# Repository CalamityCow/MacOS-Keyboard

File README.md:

# MacOS-Keyboard

Fully custom MacOS keyboard with 101 keys, 6 macro keys, 101 leds, and a volume knob. Planning to add a screen and hubs later. 

BOM: https://docs.google.com/spreadsheets/d/1dYup_cxLSYAhRu9MLTjsDp3llwcmy9G50tkykbGbxao/edit?gid=810680966#gid=810680966

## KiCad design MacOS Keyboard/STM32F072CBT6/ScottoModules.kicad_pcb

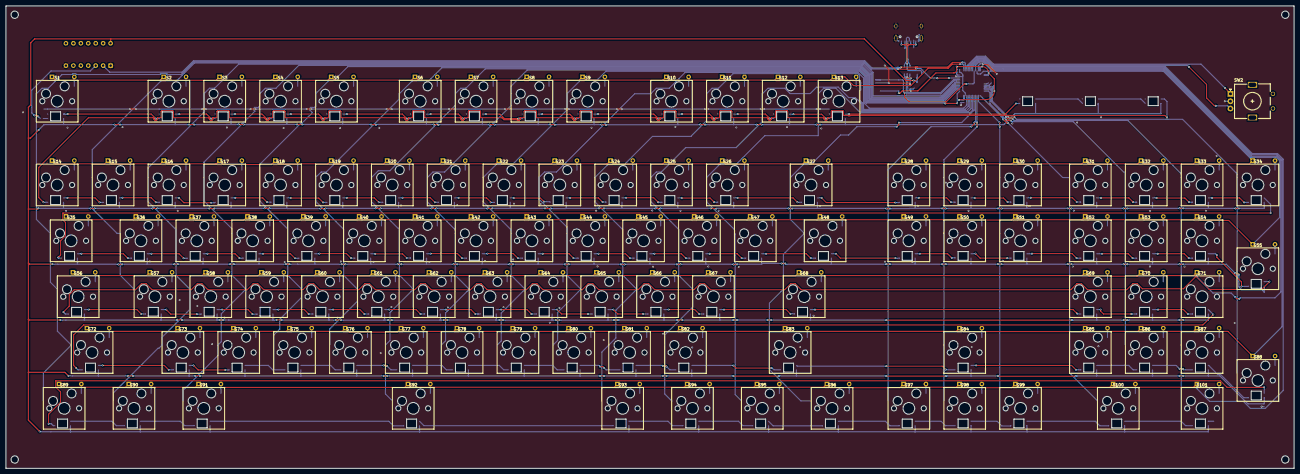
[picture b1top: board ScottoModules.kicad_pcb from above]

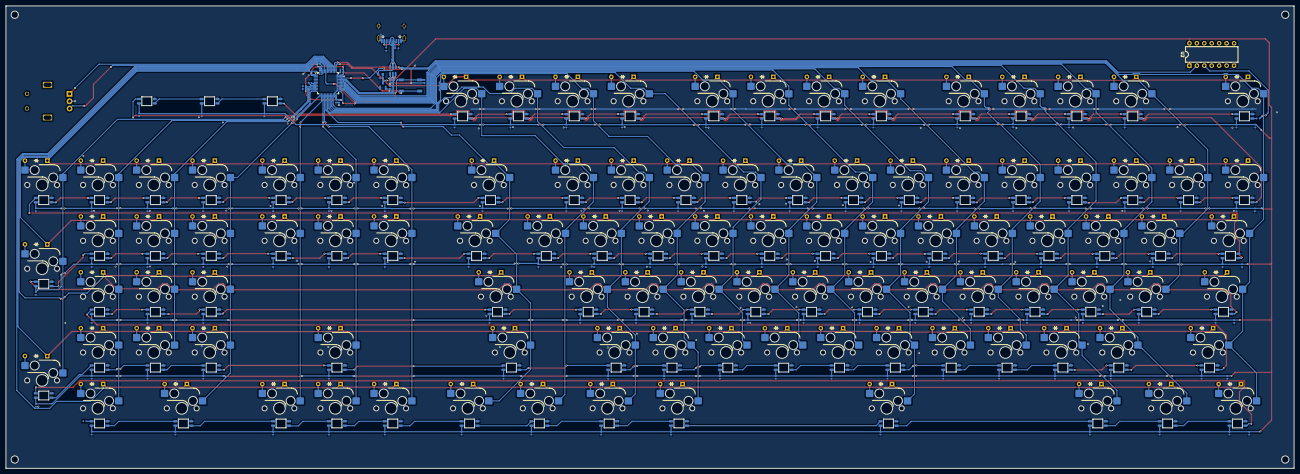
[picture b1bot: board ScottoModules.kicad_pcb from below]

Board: 2 copper layers, 439.4 x 157.7 mm, 440 parts (338 on the bottom side), 249 nets.

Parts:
C7, C10, C11, C13, C16: 100nF; Capacitor_0402
C8, C9, C15: 1uF; Capacitor_0402
C12, C17: 4.7uF; Capacitor_0402
C14: 10nF; Capacitor_0402
D1, D2, D3, D4, D5, D6, D7, D8, D9, D10, D11, D12, D13, D14, D15, D16, D17, D18, D19, D20, D21, D22, D23, D24, D25, D26, D27, D28, D29, D30, D31, D32, D33, D34, D35, D36, D37, D38, D39, D40, D41, D42, D43, D44, D45, D46, D47, D48, D49, D50, D51, D52, D53, D54, D55, D56, D57, D58, D59, D60, D61, D62, D63, D64, D65, D66, D67, D68, D69, D70, D71, D72, D73, D74, D75, D76, D77, D78, D79, D80, D81, D82, D83, D84, D85, D86, D87, D88, D89, D90, D91, D92, D93, D94, D95, D96, D97, D98, D99, D100, D101: Diode; Diode_DO-35
DisplayLED1, DisplayLED2, DisplayLED3: SK6812MINI; LED_SK6812MINI
DisplayLEDCAP1, DisplayLEDCAP2, DisplayLEDCAP3: 100nF; Capacitor_0402
F1: 500mA; Fuse_0603
J1: USB_C; USB_C_HRO_TYPE-C-31-M-12
LED1, LED2, LED3, LED4, LED5, LED6, LED7, LED8, LED9, LED10, LED11, LED12, LED13, LED14, LED15, LED16, LED17, LED18, LED19, LED20, LED21, LED22, LED23, LED24, LED25, LED26, LED27, LED28, LED29, LED30, LED31, LED32, LED33, LED34, LED35, LED36, LED37, LED38, LED39, LED40, LED41, LED42, LED43, LED44, LED45, LED46, LED47, LED48, LED49, LED50, LED51, LED52, LED53, LED54, LED55, LED56, LED57, LED58, LED59, LED60, LED61, LED62, LED63, LED64, LED65, LED66, LED67, LED68, LED69, LED70, LED71, LED72, LED73, LED74, LED75, LED76, LED77, LED78, LED79, LED80, LED81, LED82, LED83, LED84, LED85, LED86, LED87, LED88, LED89, LED90, LED91, LED92, LED93, LED94, LED95, LED96, LED97, LED98, LED99, LED100, LED101: SK6812MINI; LED_SK6812MINI
LEDBULKCAP1, LEDBULKCAP2, LEDBULKCAP3, LEDBULKCAP4, LEDBULKCAP5, LEDBULKCAP6: 100uF; Capacitor_0402
LEDCAP1, LEDCAP2, LEDCAP3, LEDCAP4, LEDCAP5, LEDCAP6, LEDCAP7, LEDCAP8, LEDCAP9, LEDCAP10, LEDCAP11, LEDCAP12, LEDCAP13, LEDCAP14, LEDCAP15, LEDCAP16, LEDCAP17, LEDCAP18, LEDCAP19, LEDCAP20, LEDCAP21, LEDCAP22, LEDCAP23, LEDCAP24, LEDCAP25, LEDCAP26, LEDCAP27, LEDCAP28, LEDCAP29, LEDCAP30, LEDCAP31, LEDCAP32, LEDCAP33, LEDCAP34, LEDCAP35, LEDCAP36, LEDCAP37, LEDCAP38, LEDCAP39, LEDCAP40, LEDCAP41, LEDCAP42, LEDCAP43, LEDCAP44, LEDCAP45, LEDCAP46, LEDCAP47, LEDCAP48, LEDCAP49, LEDCAP50, LEDCAP51, LEDCAP52, LEDCAP53, LEDCAP54, LEDCAP55, LEDCAP56, LEDCAP57, LEDCAP58, LEDCAP59, LEDCAP60, LEDCAP61, LEDCAP62, LEDCAP63, LEDCAP64, LEDCAP65, LEDCAP66, LEDCAP67, LEDCAP68, LEDCAP69, LEDCAP70, LEDCAP71, LEDCAP72, LEDCAP73, LEDCAP74, LEDCAP75, LEDCAP76, LEDCAP77, LEDCAP78, LEDCAP79, LEDCAP80, LEDCAP81, LEDCAP82, LEDCAP83, LEDCAP84, LEDCAP85, LEDCAP86, LEDCAP87, LEDCAP88, LEDCAP89, LEDCAP90, LEDCAP91, LEDCAP92, LEDCAP93, LEDCAP94, LEDCAP95, LEDCAP96, LEDCAP97, LEDCAP98, LEDCAP99, LEDCAP100, LEDCAP101: 100nF; Capacitor_0402
R1: 10k; Resistor_0402
R2, R3: 5.1k; Resistor_0402
R4, R5: 500R; Resistor_0402
S1, S2, S3, S4, S5, S6, S7, S8, S9, S10, S11, S12, S13, S14, S15, S16, S17, S18, S19, S20, S21, S22, S23, S24, S25, S26, S27, S28, S29, S30, S31, S32, S33, S34, S35, S36, S37, S38, S39, S40, S41, S42, S43, S44, S45, S46, S47, S48, S49, S50, S51, S52, S53, S54, S55, S56, S57, S58, S59, S60, S61, S62, S63, S64, S65, S66, S67, S68, S69, S70, S71, S72, S73, S74, S75, S76, S77, S78, S79, S80, S81, S82, S83, S84, S85, S86, S87, S88, S89, S90, S91, S92, S93, S94, S95, S96, S97, S98, S99, S100, S101: Keyswitch; Hotswap_MX_1.00u
SW1: SW_Push; Button_TL3342
SW2: RotaryEncoder; RotaryEncoder_Alps_EC11E_Vertical_H20mm
U1: STM32F072CBTx; LQFP-48_7x7mm_P0.5mm
U2: 74AHCT125; DIP-14_W7.62mm
U3: XC6206; Voltage_SOT-23
U4: USBLC6-2SC6; ESD_SOT-23-6

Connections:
+3.3V: C9.1, C10.2, C11.2, C12.2, C13.2, C14.2, C15.2, C16.2, C17.2, SW1.1, U1.1 (VBAT), U1.9 (VDDA), U1.24 (VDD), U1.36 (VDDIO2), U1.48 (VDD), U3.2 (VO)
+5V: C8.1, DisplayLED1.1 (VDD), DisplayLED2.1 (VDD), DisplayLED3.1 (VDD), DisplayLEDCAP1.1, DisplayLEDCAP2.1, DisplayLEDCAP3.1, F1.2, LED1.1 (VDD), LED2.1 (VDD), LED3.1 (VDD), LED4.1 (VDD), LED5.1 (VDD), LED6.1 (VDD), LED7.1 (VDD), LED8.1 (VDD), LED9.1 (VDD), LED10.1 (VDD), LED11.1 (VDD), LED12.1 (VDD), LED13.1 (VDD), LED14.1 (VDD), LED15.1 (VDD), LED16.1 (VDD), LED17.1 (VDD), LED18.1 (VDD), LED19.1 (VDD), LED20.1 (VDD), LED21.1 (VDD), LED22.1 (VDD), LED23.1 (VDD), LED24.1 (VDD), LED25.1 (VDD), LED26.1 (VDD), LED27.1 (VDD), LED28.1 (VDD), LED29.1 (VDD), LED30.1 (VDD), LED31.1 (VDD), LED32.1 (VDD), LED33.1 (VDD), LED34.1 (VDD), LED35.1 (VDD), LED36.1 (VDD), LED37.1 (VDD), LED38.1 (VDD), LED39.1 (VDD), LED40.1 (VDD), LED41.1 (VDD), LED42.1 (VDD), LED43.1 (VDD), LED44.1 (VDD), LED45.1 (VDD), LED46.1 (VDD), LED47.1 (VDD), LED48.1 (VDD), LED49.1 (VDD), LED50.1 (VDD), LED51.1 (VDD), LED52.1 (VDD), LED53.1 (VDD), LED54.1 (VDD), LED55.1 (VDD), LED56.1 (VDD), LED57.1 (VDD), LED58.1 (VDD), LED59.1 (VDD), LED60.1 (VDD), LED61.1 (VDD), LED62.1 (VDD), LED63.1 (VDD), LED64.1 (VDD), LED65.1 (VDD), LED66.1 (VDD), LED67.1 (VDD), LED68.1 (VDD), LED69.1 (VDD), LED70.1 (VDD), LED71.1 (VDD), LED72.1 (VDD), LED73.1 (VDD), LED74.1 (VDD), LED75.1 (VDD), LED76.1 (VDD), LED77.1 (VDD), LED78.1 (VDD), LED79.1 (VDD), LED80.1 (VDD), LED81.1 (VDD), LED82.1 (VDD), LED83.1 (VDD), LED84.1 (VDD), LED85.1 (VDD), LED86.1 (VDD), LED87.1 (VDD), LED88.1 (VDD), LED89.1 (VDD), LED90.1 (VDD), LED91.1 (VDD), LED92.1 (VDD), LED93.1 (VDD), LED94.1 (VDD), LED95.1 (VDD), LED96.1 (VDD), LED97.1 (VDD), LED98.1 (VDD), LED99.1 (VDD), LED100.1 (VDD), LED101.1 (VDD), LEDBULKCAP1.1, LEDBULKCAP2.1, LEDBULKCAP3.1, LEDBULKCAP4.1, LEDBULKCAP5.1, LEDBULKCAP6.1, LEDCAP1.1, LEDCAP2.1, LEDCAP3.1, LEDCAP4.1, LEDCAP5.1, LEDCAP6.1, LEDCAP7.1, LEDCAP8.1, LEDCAP9.1, LEDCAP10.1, LEDCAP11.1, LEDCAP12.1, LEDCAP13.1, LEDCAP14.1, LEDCAP15.1, LEDCAP16.1, LEDCAP17.1, LEDCAP18.1, LEDCAP19.1, LEDCAP20.1, LEDCAP21.1, LEDCAP22.1, LEDCAP23.1, LEDCAP24.1, LEDCAP25.1, LEDCAP26.1, LEDCAP27.1, LEDCAP28.1, LEDCAP29.1, LEDCAP30.1, LEDCAP31.1, LEDCAP32.1, LEDCAP33.1, LEDCAP34.1, LEDCAP35.1, LEDCAP36.1, LEDCAP37.1, LEDCAP38.1, LEDCAP39.1, LEDCAP40.1, LEDCAP41.1, LEDCAP42.1, LEDCAP43.1, LEDCAP44.1, LEDCAP45.1, LEDCAP46.1, LEDCAP47.1, LEDCAP48.1, LEDCAP49.1, LEDCAP50.1, LEDCAP51.1, LEDCAP52.1, LEDCAP53.1, LEDCAP54.1, LEDCAP55.1, LEDCAP56.1, LEDCAP57.1, LEDCAP58.1, LEDCAP59.1, LEDCAP60.1, LEDCAP61.1, LEDCAP62.1, LEDCAP63.1, LEDCAP64.1, LEDCAP65.1, LEDCAP66.1, LEDCAP67.1, LEDCAP68.1, LEDCAP69.1, LEDCAP70.1, LEDCAP71.1, LEDCAP72.1, LEDCAP73.1, LEDCAP74.1, LEDCAP75.1, LEDCAP76.1, LEDCAP77.1, LEDCAP78.1, LEDCAP79.1, LEDCAP80.1, LEDCAP81.1, LEDCAP82.1, LEDCAP83.1, LEDCAP84.1, LEDCAP85.1, LEDCAP86.1, LEDCAP87.1, LEDCAP88.1, LEDCAP89.1, LEDCAP90.1, LEDCAP91.1, LEDCAP92.1, LEDCAP93.1, LEDCAP94.1, LEDCAP95.1, LEDCAP96.1, LEDCAP97.1, LEDCAP98.1, LEDCAP99.1, LEDCAP100.1, LEDCAP101.1, U2.14 (VCC), U3.3 (VI)
/A15: U1.38 (PA15), U2.2
/B3: SW2.A, U1.39 (PB3)
/B4: SW2.B, U1.40 (PB4)
/BOOT0: R1.2, SW1.2, U1.44 (BOOT0)
/LED/DIN: R4.1, U2.3
/MCU_D+: U1.33 (PA12), U4.1 (I/O1)
/MCU_D-: U1.32 (PA11), U4.3 (I/O2)
/NRST: C7.1, U1.7 (NRST)
/USB_D+: J1.A6 (D+), J1.B6 (D+), U4.6 (I/O1)
/USB_D-: J1.A7 (D-), J1.B7 (D-), U4.4 (I/O2)
A0: S34.1, S55.1, S88.1, U1.10 (PA0)
A1: S33.1, S54.1, S71.1, S87.1, S101.1, U1.11 (PA1)
A2: S32.1, S53.1, S70.1, S86.1, U1.12 (PA2)
A3: S31.1, S52.1, S69.1, S85.1, S100.1, U1.13 (PA3)
A4: S30.1, S51.1, S99.1, U1.14 (PA4)
A5: S29.1, S50.1, S84.1, S98.1, U1.15 (PA5)
A6: S28.1, S49.1, S97.1, U1.16 (PA6)
A7: S27.1, S48.1, S68.1, S83.1, S96.1, U1.17 (PA7)
A8: S4.1, S17.1, S38.1, S59.1, S74.1, S91.1, U1.29 (PA8)
A9: S3.1, S16.1, S37.1, S58.1, S73.1, S90.1, U1.30 (PA9)
A10: S2.1, S15.1, S36.1, S57.1, U1.31 (PA10)
A13: S1.1, S14.1, S35.1, S56.1, S72.1, S89.1, U1.34 (PA13)
A14: D1.1 (K), D2.1 (K), D3.1 (K), D4.1 (K), D5.1 (K), D6.1 (K), D7.1 (K), D8.1 (K), D9.1 (K), D10.1 (K), D11.1 (K), D12.1 (K), D13.1 (K), U1.37 (PA14)
B0: S13.1, S26.1, S47.1, S95.1, U1.18 (PB0)
B1: S12.1, S25.1, S46.1, S67.1, S82.1, S94.1, U1.19 (PB1)
B2: S11.1, S24.1, S45.1, S66.1, S81.1, S93.1, U1.20 (PB2)
B5: D89.1 (K), D90.1 (K), D91.1 (K), D92.1 (K), D93.1 (K), D94.1 (K), D95.1 (K), D96.1 (K), D97.1 (K), D98.1 (K), D99.1 (K), D100.1 (K), D101.1 (K), U1.41 (PB5)
B6: D72.1 (K), D73.1 (K), D74.1 (K), D75.1 (K), D76.1 (K), D77.1 (K), D78.1 (K), D79.1 (K), D80.1 (K), D81.1 (K), D82.1 (K), D83.1 (K), D84.1 (K), D85.1 (K), D86.1 (K), D87.1 (K), D88.1 (K), U1.42 (PB6)
B7: D56.1 (K), D57.1 (K), D58.1 (K), D59.1 (K), D60.1 (K), D61.1 (K), D62.1 (K), D63.1 (K), D64.1 (K), D65.1 (K), D66.1 (K), D67.1 (K), D68.1 (K), D69.1 (K), D70.1 (K), D71.1 (K), U1.43 (PB7)
B8: D35.1 (K), D36.1 (K), D37.1 (K), D38.1 (K), D39.1 (K), D40.1 (K), D41.1 (K), D42.1 (K), D43.1 (K), D44.1 (K), D45.1 (K), D46.1 (K), D47.1 (K), D48.1 (K), D49.1 (K), D50.1 (K), D51.1 (K), D52.1 (K), D53.1 (K), D54.1 (K), D55.1 (K), U1.45 (PB8)
B9: D14.1 (K), D15.1 (K), D16.1 (K), D17.1 (K), D18.1 (K), D19.1 (K), D20.1 (K), D21.1 (K), D22.1 (K), D23.1 (K), D24.1 (K), D25.1 (K), D26.1 (K), D27.1 (K), D28.1 (K), D29.1 (K), D30.1 (K), D31.1 (K), D32.1 (K), D33.1 (K), D34.1 (K), U1.46 (PB9)
B10: S10.1, S23.1, S44.1, S65.1, S80.1, U1.21 (PB10)
B11: S9.1, S22.1, S43.1, S64.1, S79.1, U1.22 (PB11)
B12: S8.1, S21.1, S42.1, S63.1, S78.1, U1.25 (PB12)
B13: S7.1, S20.1, S41.1, S62.1, S77.1, S92.1, U1.26 (PB13)
B14: S6.1, S19.1, S40.1, S61.1, S76.1, U1.27 (PB14)
B15: S5.1, S18.1, S39.1, S60.1, S75.1, U1.28 (PB15)
D1: DisplayLED3.2 (DOUT), LED14.4 (DIN)
D2: LED34.2 (DOUT), LED35.4 (DIN)
D3: LED55.2 (DOUT), LED56.4 (DIN)
D4: LED71.2 (DOUT), LED72.4 (DIN)
D5: LED88.2 (DOUT), LED89.4 (DIN)
GND: C7.2, C8.2, C9.2, C10.1, C11.1, C12.1, C13.1, C14.1, C15.1, C16.1, C17.1, DisplayLED1.3 (VSS), DisplayLED2.3 (VSS), DisplayLED3.3 (VSS), DisplayLEDCAP1.2, DisplayLEDCAP2.2, DisplayLEDCAP3.2, J1.A1 (GND), J1.A12 (GND), J1.B1 (GND), J1.B12 (GND), J1.S1 (SHIELD), LED1.3 (VSS), LED2.3 (VSS), LED3.3 (VSS), LED4.3 (VSS), LED5.3 (VSS), LED6.3 (VSS), LED7.3 (VSS), LED8.3 (VSS), LED9.3 (VSS), LED10.3 (VSS), LED11.3 (VSS), LED12.3 (VSS), LED13.3 (VSS), LED14.3 (VSS), LED15.3 (VSS), LED16.3 (VSS), LED17.3 (VSS), LED18.3 (VSS), LED19.3 (VSS), LED20.3 (VSS), LED21.3 (VSS), LED22.3 (VSS), LED23.3 (VSS), LED24.3 (VSS), LED25.3 (VSS), LED26.3 (VSS), LED27.3 (VSS), LED28.3 (VSS), LED29.3 (VSS), LED30.3 (VSS), LED31.3 (VSS), LED32.3 (VSS), LED33.3 (VSS), LED34.3 (VSS), LED35.3 (VSS), LED36.3 (VSS), LED37.3 (VSS), LED38.3 (VSS), LED39.3 (VSS), LED40.3 (VSS), LED41.3 (VSS), LED42.3 (VSS), LED43.3 (VSS), LED44.3 (VSS), LED45.3 (VSS), LED46.3 (VSS), LED47.3 (VSS), LED48.3 (VSS), LED49.3 (VSS), LED50.3 (VSS), LED51.3 (VSS), LED52.3 (VSS), LED53.3 (VSS), LED54.3 (VSS), LED55.3 (VSS), LED56.3 (VSS), LED57.3 (VSS), LED58.3 (VSS), LED59.3 (VSS), LED60.3 (VSS), LED61.3 (VSS), LED62.3 (VSS), LED63.3 (VSS), LED64.3 (VSS), LED65.3 (VSS), LED66.3 (VSS), LED67.3 (VSS), LED68.3 (VSS), LED69.3 (VSS), LED70.3 (VSS), LED71.3 (VSS), LED72.3 (VSS), LED73.3 (VSS), LED74.3 (VSS), LED75.3 (VSS), LED76.3 (VSS), LED77.3 (VSS), LED78.3 (VSS), LED79.3 (VSS), LED80.3 (VSS), LED81.3 (VSS), LED82.3 (VSS), LED83.3 (VSS), LED84.3 (VSS), LED85.3 (VSS), LED86.3 (VSS), LED87.3 (VSS), LED88.3 (VSS), LED89.3 (VSS), LED90.3 (VSS), LED91.3 (VSS), LED92.3 (VSS), LED93.3 (VSS), LED94.3 (VSS), LED95.3 (VSS), LED96.3 (VSS), LED97.3 (VSS), LED98.3 (VSS), LED99.3 (VSS), LED100.3 (VSS), LED101.3 (VSS), LEDBULKCAP1.2, LEDBULKCAP2.2, LEDBULKCAP3.2, LEDBULKCAP4.2, LEDBULKCAP5.2, LEDBULKCAP6.2, LEDCAP1.2, LEDCAP2.2, LEDCAP3.2, LEDCAP4.2, LEDCAP5.2, LEDCAP6.2, LEDCAP7.2, LEDCAP8.2, LEDCAP9.2, LEDCAP10.2, LEDCAP11.2, LEDCAP12.2, LEDCAP13.2, LEDCAP14.2, LEDCAP15.2, LEDCAP16.2, LEDCAP17.2, LEDCAP18.2, LEDCAP19.2, LEDCAP20.2, LEDCAP21.2, LEDCAP22.2, LEDCAP23.2, LEDCAP24.2, LEDCAP25.2, LEDCAP26.2, LEDCAP27.2, LEDCAP28.2, LEDCAP29.2, LEDCAP30.2, LEDCAP31.2, LEDCAP32.2, LEDCAP33.2, LEDCAP34.2, LEDCAP35.2, LEDCAP36.2, LEDCAP37.2, LEDCAP38.2, LEDCAP39.2, LEDCAP40.2, LEDCAP41.2, LEDCAP42.2, LEDCAP43.2, LEDCAP44.2, LEDCAP45.2, LEDCAP46.2, LEDCAP47.2, LEDCAP48.2, LEDCAP49.2, LEDCAP50.2, LEDCAP51.2, LEDCAP52.2, LEDCAP53.2, LEDCAP54.2, LEDCAP55.2, LEDCAP56.2, LEDCAP57.2, LEDCAP58.2, LEDCAP59.2, LEDCAP60.2, LEDCAP61.2, LEDCAP62.2, LEDCAP63.2, LEDCAP64.2, LEDCAP65.2, LEDCAP66.2, LEDCAP67.2, LEDCAP68.2, LEDCAP69.2, LEDCAP70.2, LEDCAP71.2, LEDCAP72.2, LEDCAP73.2, LEDCAP74.2, LEDCAP75.2, LEDCAP76.2, LEDCAP77.2, LEDCAP78.2, LEDCAP79.2, LEDCAP80.2, LEDCAP81.2, LEDCAP82.2, LEDCAP83.2, LEDCAP84.2, LEDCAP85.2, LEDCAP86.2, LEDCAP87.2, LEDCAP88.2, LEDCAP89.2, LEDCAP90.2, LEDCAP91.2, LEDCAP92.2, LEDCAP93.2, LEDCAP94.2, LEDCAP95.2, LEDCAP96.2, LEDCAP97.2, LEDCAP98.2, LEDCAP99.2, LEDCAP100.2, LEDCAP101.2, R1.1, R2.2, R3.2, SW2.C, U1.8 (VSSA), U1.23 (VSS), U1.35 (VSS), U1.47 (VSS), U2.1, U2.7 (GND), U3.1 (GND), U4.2 (GND)
unnamed: D1.2 (A), S1.2
unnamed: D2.2 (A), S2.2
unnamed: D3.2 (A), S3.2
unnamed: D4.2 (A), S4.2
unnamed: D5.2 (A), S5.2
unnamed: D6.2 (A), S6.2
unnamed: D7.2 (A), S7.2
unnamed: D8.2 (A), S8.2
unnamed: D9.2 (A), S9.2
unnamed: D10.2 (A), S10.2
unnamed: D11.2 (A), S11.2
unnamed: D12.2 (A), S12.2
unnamed: D13.2 (A), S13.2
unnamed: D14.2 (A), S14.2
unnamed: D15.2 (A), S15.2
unnamed: D16.2 (A), S16.2
unnamed: D17.2 (A), S17.2
unnamed: D18.2 (A), S18.2
unnamed: D19.2 (A), S19.2
unnamed: D20.2 (A), S20.2
unnamed: D21.2 (A), S21.2
unnamed: D22.2 (A), S22.2
unnamed: D23.2 (A), S23.2
unnamed: D24.2 (A), S24.2
unnamed: D25.2 (A), S25.2
unnamed: D26.2 (A), S26.2
unnamed: D27.2 (A), S27.2
unnamed: D28.2 (A), S28.2
unnamed: D29.2 (A), S29.2
unnamed: D30.2 (A), S30.2
unnamed: D31.2 (A), S31.2
unnamed: D32.2 (A), S32.2
unnamed: D33.2 (A), S33.2
unnamed: D34.2 (A), S34.2
unnamed: D35.2 (A), S35.2
unnamed: D36.2 (A), S36.2
unnamed: D37.2 (A), S37.2
unnamed: D38.2 (A), S38.2
unnamed: D39.2 (A), S39.2
unnamed: D40.2 (A), S40.2
unnamed: D41.2 (A), S41.2
unnamed: D42.2 (A), S42.2
unnamed: D43.2 (A), S43.2
unnamed: D44.2 (A), S44.2
unnamed: D45.2 (A), S45.2
unnamed: D46.2 (A), S46.2
unnamed: D47.2 (A), S47.2
unnamed: D48.2 (A), S48.2
unnamed: D49.2 (A), S49.2
unnamed: D50.2 (A), S50.2
unnamed: D51.2 (A), S51.2
unnamed: D52.2 (A), S52.2
unnamed: D53.2 (A), S53.2
unnamed: D54.2 (A), S54.2
unnamed: D55.2 (A), S55.2
unnamed: D56.2 (A), S56.2
unnamed: D57.2 (A), S57.2
unnamed: D58.2 (A), S58.2
unnamed: D59.2 (A), S59.2
unnamed: D60.2 (A), S60.2
unnamed: D61.2 (A), S61.2
unnamed: D62.2 (A), S62.2
unnamed: D63.2 (A), S63.2
unnamed: D64.2 (A), S64.2
unnamed: D65.2 (A), S65.2
unnamed: D66.2 (A), S66.2
unnamed: D67.2 (A), S67.2
unnamed: D68.2 (A), S68.2
unnamed: D69.2 (A), S69.2
unnamed: D70.2 (A), S70.2
unnamed: D71.2 (A), S71.2
unnamed: D72.2 (A), S72.2
unnamed: D73.2 (A), S73.2
unnamed: D74.2 (A), S74.2
unnamed: D75.2 (A), S75.2
unnamed: D76.2 (A), S76.2
unnamed: D77.2 (A), S77.2
unnamed: D78.2 (A), S78.2
unnamed: D79.2 (A), S79.2
unnamed: D80.2 (A), S80.2
unnamed: D81.2 (A), S81.2
unnamed: D82.2 (A), S82.2
unnamed: D83.2 (A), S83.2
unnamed: D84.2 (A), S84.2
unnamed: D85.2 (A), S85.2
unnamed: D86.2 (A), S86.2
unnamed: D87.2 (A), S87.2
unnamed: D88.2 (A), S88.2
unnamed: D89.2 (A), S89.2
unnamed: D90.2 (A), S90.2
unnamed: D91.2 (A), S91.2
unnamed: D92.2 (A), S92.2
unnamed: D93.2 (A), S93.2
unnamed: D94.2 (A), S94.2
unnamed: D95.2 (A), S95.2
unnamed: D96.2 (A), S96.2
unnamed: D97.2 (A), S97.2
unnamed: D98.2 (A), S98.2
unnamed: D99.2 (A), S99.2
unnamed: D100.2 (A), S100.2
unnamed: D101.2 (A), S101.2
unnamed: DisplayLED1.4 (DIN), LED13.2 (DOUT)
unnamed: DisplayLED1.2 (DOUT), DisplayLED2.4 (DIN)
unnamed: DisplayLED2.2 (DOUT), DisplayLED3.4 (DIN)
unnamed: J1.A5 (CC1), R2.1
unnamed: J1.B5 (CC2), R3.1
unnamed: LED1.4 (DIN), R4.2
unnamed: LED1.2 (DOUT), LED2.4 (DIN)
unnamed: LED2.2 (DOUT), LED3.4 (DIN)
unnamed: LED3.2 (DOUT), LED4.4 (DIN)
unnamed: LED4.2 (DOUT), LED5.4 (DIN)
unnamed: LED5.2 (DOUT), LED6.4 (DIN)
unnamed: LED6.2 (DOUT), LED7.4 (DIN)
unnamed: LED7.2 (DOUT), LED8.4 (DIN)
unnamed: LED8.2 (DOUT), LED9.4 (DIN)
unnamed: LED9.2 (DOUT), LED10.4 (DIN)
unnamed: LED10.2 (DOUT), LED11.4 (DIN)
unnamed: LED11.2 (DOUT), LED12.4 (DIN)
unnamed: LED12.2 (DOUT), LED13.4 (DIN)
unnamed: LED14.2 (DOUT), LED15.4 (DIN)
unnamed: LED15.2 (DOUT), LED16.4 (DIN)
unnamed: LED16.2 (DOUT), LED17.4 (DIN)
unnamed: LED17.2 (DOUT), LED18.4 (DIN)
unnamed: LED18.2 (DOUT), LED19.4 (DIN)
unnamed: LED19.2 (DOUT), LED20.4 (DIN)
unnamed: LED20.2 (DOUT), LED21.4 (DIN)
unnamed: LED21.2 (DOUT), LED22.4 (DIN)
unnamed: LED22.2 (DOUT), LED23.4 (DIN)
unnamed: LED23.2 (DOUT), LED24.4 (DIN)
unnamed: LED24.2 (DOUT), LED25.4 (DIN)
unnamed: LED25.2 (DOUT), LED26.4 (DIN)
unnamed: LED26.2 (DOUT), LED27.4 (DIN)
unnamed: LED27.2 (DOUT), LED28.4 (DIN)
unnamed: LED28.2 (DOUT), LED29.4 (DIN)
unnamed: LED29.2 (DOUT), LED30.4 (DIN)
unnamed: LED30.2 (DOUT), LED31.4 (DIN)
unnamed: LED31.2 (DOUT), LED32.4 (DIN)
unnamed: LED32.2 (DOUT), LED33.4 (DIN)
unnamed: LED33.2 (DOUT), LED34.4 (DIN)
unnamed: LED35.2 (DOUT), LED36.4 (DIN)
unnamed: LED36.2 (DOUT), LED37.4 (DIN)
unnamed: LED37.2 (DOUT), LED38.4 (DIN)
unnamed: LED38.2 (DOUT), LED39.4 (DIN)
unnamed: LED39.2 (DOUT), LED40.4 (DIN)
unnamed: LED40.2 (DOUT), LED41.4 (DIN)
unnamed: LED41.2 (DOUT), LED42.4 (DIN)
unnamed: LED42.2 (DOUT), LED43.4 (DIN)
unnamed: LED43.2 (DOUT), LED44.4 (DIN)
unnamed: LED44.2 (DOUT), LED45.4 (DIN)
unnamed: LED45.2 (DOUT), LED46.4 (DIN)
unnamed: LED46.2 (DOUT), LED47.4 (DIN)
unnamed: LED47.2 (DOUT), LED48.4 (DIN)
unnamed: LED48.2 (DOUT), LED49.4 (DIN)
unnamed: LED49.2 (DOUT), LED50.4 (DIN)
unnamed: LED50.2 (DOUT), LED51.4 (DIN)
unnamed: LED51.2 (DOUT), LED52.4 (DIN)
unnamed: LED52.2 (DOUT), LED53.4 (DIN)
unnamed: LED53.2 (DOUT), LED54.4 (DIN)
unnamed: LED54.2 (DOUT), LED55.4 (DIN)
unnamed: LED56.2 (DOUT), LED57.4 (DIN)
unnamed: LED57.2 (DOUT), LED58.4 (DIN)
unnamed: LED58.2 (DOUT), LED59.4 (DIN)
unnamed: LED59.2 (DOUT), LED60.4 (DIN)
unnamed: LED60.2 (DOUT), LED61.4 (DIN)
unnamed: LED61.2 (DOUT), LED62.4 (DIN)
unnamed: LED62.2 (DOUT), LED63.4 (DIN)
unnamed: LED63.2 (DOUT), LED64.4 (DIN)
unnamed: LED64.2 (DOUT), LED65.4 (DIN)
unnamed: LED65.2 (DOUT), LED66.4 (DIN)
unnamed: LED66.2 (DOUT), LED67.4 (DIN)
unnamed: LED67.2 (DOUT), LED68.4 (DIN)
unnamed: LED68.2 (DOUT), LED69.4 (DIN)
unnamed: LED69.2 (DOUT), LED70.4 (DIN)
unnamed: LED70.2 (DOUT), LED71.4 (DIN)
unnamed: LED72.2 (DOUT), LED73.4 (DIN)
unnamed: LED73.2 (DOUT), LED74.4 (DIN)
unnamed: LED74.2 (DOUT), LED75.4 (DIN)
unnamed: LED75.2 (DOUT), LED76.4 (DIN)
unnamed: LED76.2 (DOUT), LED77.4 (DIN)
unnamed: LED77.2 (DOUT), LED78.4 (DIN)
unnamed: LED78.2 (DOUT), LED79.4 (DIN)
unnamed: LED79.2 (DOUT), LED80.4 (DIN)
unnamed: LED80.2 (DOUT), LED81.4 (DIN)
unnamed: LED81.2 (DOUT), LED82.4 (DIN)
unnamed: LED82.2 (DOUT), LED83.4 (DIN)
unnamed: LED83.2 (DOUT), LED84.4 (DIN)
unnamed: LED84.2 (DOUT), LED85.4 (DIN)
unnamed: LED85.2 (DOUT), LED86.4 (DIN)
unnamed: LED86.2 (DOUT), LED87.4 (DIN)
unnamed: LED87.2 (DOUT), LED88.4 (DIN)
unnamed: LED89.2 (DOUT), LED90.4 (DIN)
unnamed: LED90.2 (DOUT), LED91.4 (DIN)
unnamed: LED91.2 (DOUT), LED92.4 (DIN)
unnamed: LED92.2 (DOUT), LED93.4 (DIN)
unnamed: LED93.2 (DOUT), LED94.4 (DIN)
unnamed: LED94.2 (DOUT), LED95.4 (DIN)
unnamed: LED95.2 (DOUT), LED96.4 (DIN)
unnamed: LED96.2 (DOUT), LED97.4 (DIN)
unnamed: LED97.2 (DOUT), LED98.4 (DIN)
unnamed: LED98.2 (DOUT), LED99.4 (DIN)
unnamed: LED99.2 (DOUT), LED100.4 (DIN)
unnamed: LED100.2 (DOUT), LED101.4 (DIN)
unnamed: LED101.2 (DOUT), R5.1
VBUS: F1.1, J1.A4 (VBUS), J1.A9 (VBUS), J1.B4 (VBUS), J1.B9 (VBUS), U4.5 (VBUS)

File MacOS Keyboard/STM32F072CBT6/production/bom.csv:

Designator,Footprint,Quantity,Value,LCSC Part #
"C10, C11, C13, C16, C7",Capacitor_0402,5,100nF,C307331
"C12, C17",Capacitor_0402,2,4.7uF,C23733
C14,Capacitor_0402,1,10nF,C15195
"C15, C8, C9",Capacitor_0402,3,1uF,C52923
"D1, D10, D100, D101, D11, D12, D13, D14, D15, D16, D17, D18, D19, D2, D20, D21, D22, D23, D24, D25, D26, D27, D28, D29, D3, D30, D31, D32, D33, D34, D35, D36, D37, D38, D39, D4, D40, D41, D42, D43, D44, D45, D46, D47, D48, D49, D5, D50, D51, D52, D53, D54, D55, D56, D57, D58, D59, D6, D60, D61, D62, D63, D64, D65, D66, D67, D68, D69, D7, D70, D71, D72, D73, D74, D75, D76, D77, D78, D79, D8, D80, D81, D82, D83, D84, D85, D86, D87, D88, D89, D9, D90, D91, D92, D93, D94, D95, D96, D97, D98, D99",Diode_DO-35,101,Diode,
"DISPLAYLED1, DISPLAYLED2, DISPLAYLED3, LED1, LED10, LED100, LED101, LED11, LED12, LED13, LED14, LED15, LED16, LED17, LED18, LED19, LED2, LED20, LED21, LED22, LED23, LED24, LED25, LED26, LED27, LED28, LED29, LED3, LED30, LED31, LED32, LED33, LED34, LED35, LED36, LED37, LED38, LED39, LED4, LED40, LED41, LED42, LED43, LED44, LED45, LED46, LED47, LED48, LED49, LED5, LED50, LED51, LED52, LED53, LED54, LED55, LED56, LED57, LED58, LED59, LED6, LED60, LED61, LED62, LED63, LED64, LED65, LED66, LED67, LED68, LED69, LED7, LED70, LED71, LED72, LED73, LED74, LED75, LED76, LED77, LED78, LED79, LED8, LED80, LED81, LED82, LED83, LED84, LED85, LED86, LED87, LED88, LED89, LED9, LED90, LED91, LED92, LED93, LED94, LED95, LED96, LED97, LED98, LED99",LED_SK6812MINI,104,SK6812MINI,C5149201
"DISPLAYLEDCAP1, DISPLAYLEDCAP2, DISPLAYLEDCAP3, LEDCAP1, LEDCAP10, LEDCAP100, LEDCAP101, LEDCAP11, LEDCAP12, LEDCAP13, LEDCAP14, LEDCAP15, LEDCAP16, LEDCAP17, LEDCAP18, LEDCAP19, LEDCAP2, LEDCAP20, LEDCAP21, LEDCAP22, LEDCAP23, LEDCAP24, LEDCAP25, LEDCAP26, LEDCAP27, LEDCAP28, LEDCAP29, LEDCAP3, LEDCAP30, LEDCAP31, LEDCAP32, LEDCAP33, LEDCAP34, LEDCAP35, LEDCAP36, LEDCAP37, LEDCAP38, LEDCAP39, LEDCAP4, LEDCAP40, LEDCAP41, LEDCAP42, LEDCAP43, LEDCAP44, LEDCAP45, LEDCAP46, LEDCAP47, LEDCAP48, LEDCAP49, LEDCAP5, LEDCAP50, LEDCAP51, LEDCAP52, LEDCAP53, LEDCAP54, LEDCAP55, LEDCAP56, LEDCAP57, LEDCAP58, LEDCAP59, LEDCAP6, LEDCAP60, LEDCAP61, LEDCAP62, LEDCAP63, LEDCAP64, LEDCAP65, LEDCAP66, LEDCAP67, LEDCAP68, LEDCAP69, LEDCAP7, LEDCAP70, LEDCAP71, LEDCAP72, LEDCAP73, LEDCAP74, LEDCAP75, LEDCAP76, LEDCAP77, LEDCAP78, LEDCAP79, LEDCAP8, LEDCAP80, LEDCAP81, LEDCAP82, LEDCAP83, LEDCAP84, LEDCAP85, LEDCAP86, LEDCAP87, LEDCAP88, LEDCAP89, LEDCAP9, LEDCAP90, LEDCAP91, LEDCAP92, LEDCAP93, LEDCAP94, LEDCAP95, LEDCAP96, LEDCAP97, LEDCAP98, LEDCAP99",Capacitor_0402,104,100nF,
F1,Fuse_0603,1,500mA,C210357
J1,USB_C_HRO_TYPE-C-31-M-12,1,USB_C,C165948
"LEDBULKCAP1, LEDBULKCAP2, LEDBULKCAP3, LEDBULKCAP4, LEDBULKCAP5, LEDBULKCAP6",Capacitor_0402,6,100uF,
R1,Resistor_0402,1,10k,C25744
"R2, R3",Resistor_0402,2,5.1k,
"R4, R5",Resistor_0402,2,500R,
"S1, S10, S100, S101, S11, S12, S13, S14, S15, S16, S17, S18, S19, S2, S20, S21, S22, S23, S24, S25, S26, S27, S28, S29, S3, S30, S31, S32, S33, S34, S35, S36, S37, S38, S39, S4, S40, S41, S42, S43, S44, S45, S46, S47, S48, S49, S5, S50, S51, S52, S53, S54, S55, S56, S57, S58, S59, S6, S60, S61, S62, S63, S64, S65, S66, S67, S68, S69, S7, S70, S71, S72, S73, S74, S75, S76, S77, S78, S79, S8, S80, S81, S82, S83, S84, S85, S86, S87, S88, S89, S9, S90, S91, S92, S93, S94, S95, S96, S97, S98, S99",Hotswap_MX_1.00u,101,Keyswitch,
SW1,Button_TL3342,1,SW_Push,C115351
SW2,RotaryEncoder_Alps_EC11E_Vertical_H20mm,1,RotaryEncoder,
U1,LQFP-48_7x7mm_P0.5mm,1,STM32F072CBTx,
U2,DIP-14_W7.62mm,1,74AHCT125,
U3,Voltage_SOT-23,1,XC6206,C5446
U4,ESD_SOT-23-6,1,USBLC6-2SC6,C2827654

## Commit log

2025-11-24 commit 1
2025-11-30 things
2025-12-06 asdasda
2025-12-06 i did things
2025-12-07 Revert "i did things"
    This reverts commit bd682275bb3cd265989c9030c0e4774eec635702.
